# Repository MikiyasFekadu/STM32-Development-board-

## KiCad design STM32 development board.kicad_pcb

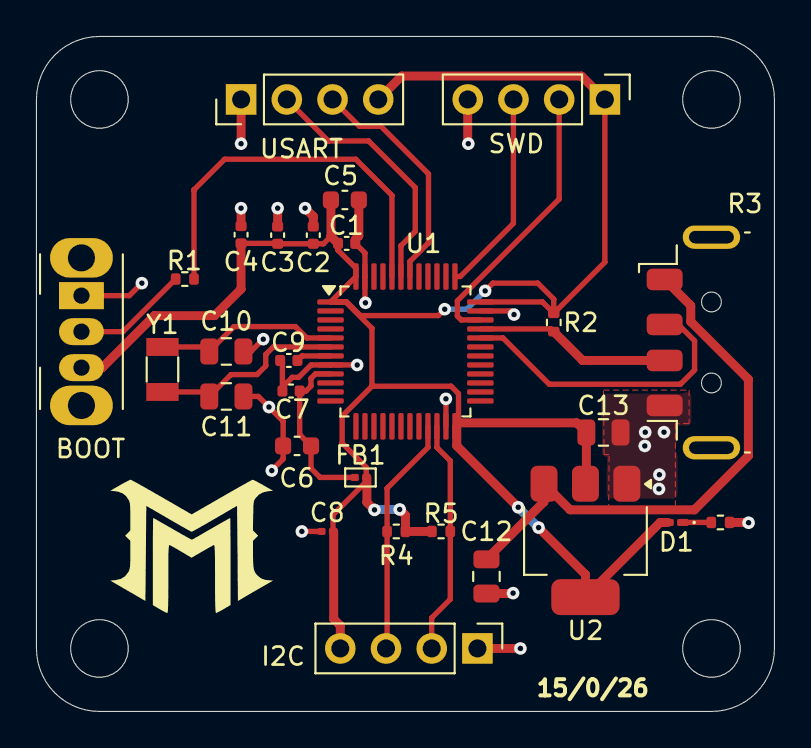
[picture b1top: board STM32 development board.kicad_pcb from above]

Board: 2 copper layers, 41.0 x 37.5 mm, 32 parts (0 on the bottom side), 18 nets.

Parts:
BOOT: SW_SPDT; SW_Slide_SPDT_Angled_CK_OS102011MA1Q
C1, C2, C3, C4, C9: 100nF; C_0402_1005Metric
C5, C6: 10uF; C_0603_1608Metric
C7: 1uF; C_0402_1005Metric
C8: 1uF; C_0201_0603Metric
C10, C11, C12, C13: 22pF; C_0805_2012Metric
D1: LED; LED_0201_0603Metric_Pad0.64x0.40mm_HandSolder
FB1: 120R; Ferrite_0201_0603Metric
H1, H2, H3, H4: MountingHole_M3; MountingHole_3.2mm_M3
I2C: I2C; PinHeader_1x04_P2.54mm_Vertical
J1: USB_A; USB A
R1: 10kR; R_0402_1005Metric
R2, R3, R4, R5: 1k5; R_0402_1005Metric
SWD: ST-Link; PinHeader_1x04_P2.54mm_Vertical
U1: STM32F103C8Tx; LQFP-48_7x7mm_P0.5mm
U2: AMS1117-3.3; SOT-223-3_TabPin2
USART: USART; PinHeader_1x04_P2.54mm_Vertical
Y1: Crystal_16MHz; Crystal_SMD_3215-2Pin_3.2x1.5mm

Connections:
+3.3V: BOOT.3 (C), C1.2, C2.2, C3.2, C4.2, C5.2, C8.2, C13.2, D1.2, FB1.2, I2C.4, R2.2, R4.2, R5.2, SWD.1, U1.1 (VBAT), U1.24 (VDD), U1.36 (VDD), U1.48 (VDD), U2.2 (VO), USART.4
+3.3VA: C6.2, C7.2, FB1.1, U1.9 (VDDA)
/BOOT0: R1.2, U1.44 (BOOT0)
/I2C1_SCL: I2C.3, R4.1, U1.21 (PB10)
/I2C1_SDA: I2C.2, R5.1, U1.22 (PB11)
/LED_cat: D1.1, R3.2
/NRST: C9.2, U1.7 (NRST)
/OSC1: C10.1, U1.5 (PD0), Y1.1
/OSC2: C11.2, U1.6 (PD1), Y1.2
/SWCLK: SWD.3, U1.37 (PA14)
/SWDIO: SWD.2, U1.34 (PA13)
/SW_BOOT0: BOOT.2 (B), R1.1
/USART1_RX: U1.43 (PB7), USART.2
/USART1_TX: U1.42 (PB6), USART.3
/USB_D+: J1.3 (D+), R2.1, U1.33 (PA12)
/USB_D-: J1.2 (D-), U1.32 (PA11)
GND: BOOT.1 (A), C1.1, C2.1, C3.1, C4.1, C5.1, C6.1, C7.1, C8.1, C9.1, C10.2, C11.1, C12.2, C13.1, I2C.1, J1.4 (GND), R3.1, SWD.4, U1.8 (VSSA), U1.23 (VSS), U1.35 (VSS), U1.47 (VSS), U2.1 (GND), USART.1
VBUS: C12.1, J1.1 (VBUS), U2.3 (VI)
